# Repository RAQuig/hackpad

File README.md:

# hackpad
This respository was created by RAQuig for the project "Hackpad" by the charity Hack Club.
It is designed with three keyboard switches and USB input.
The repository currently includes:
    --> KiCAD files (.pcb, .prl, .pro, .sch, .sch-bak)
    --> 3D Print Files (.glb, .stl)
    --> QMK Configuration Files for firmware (potentially unstable release)
    --> The Bill of Materials (BOMCSV.csv)

README:
Description: This project is a very small homemade version of a Stream Deck. It has three keys that can be programmed and a small OLED display (0.91").
Why: I have always wanted to create my own technology and this project is my way in to the rest of it. I hope this project helps me learn a lot about how technology works.
How to use: Connect the USB cable to a laptop, PC, or (hopefully) console to get three keybinds to be used how I used and a OLED screen for some stats (controller battery level, FPS, Stream stats, etc.)

PCB: 
Schematic:

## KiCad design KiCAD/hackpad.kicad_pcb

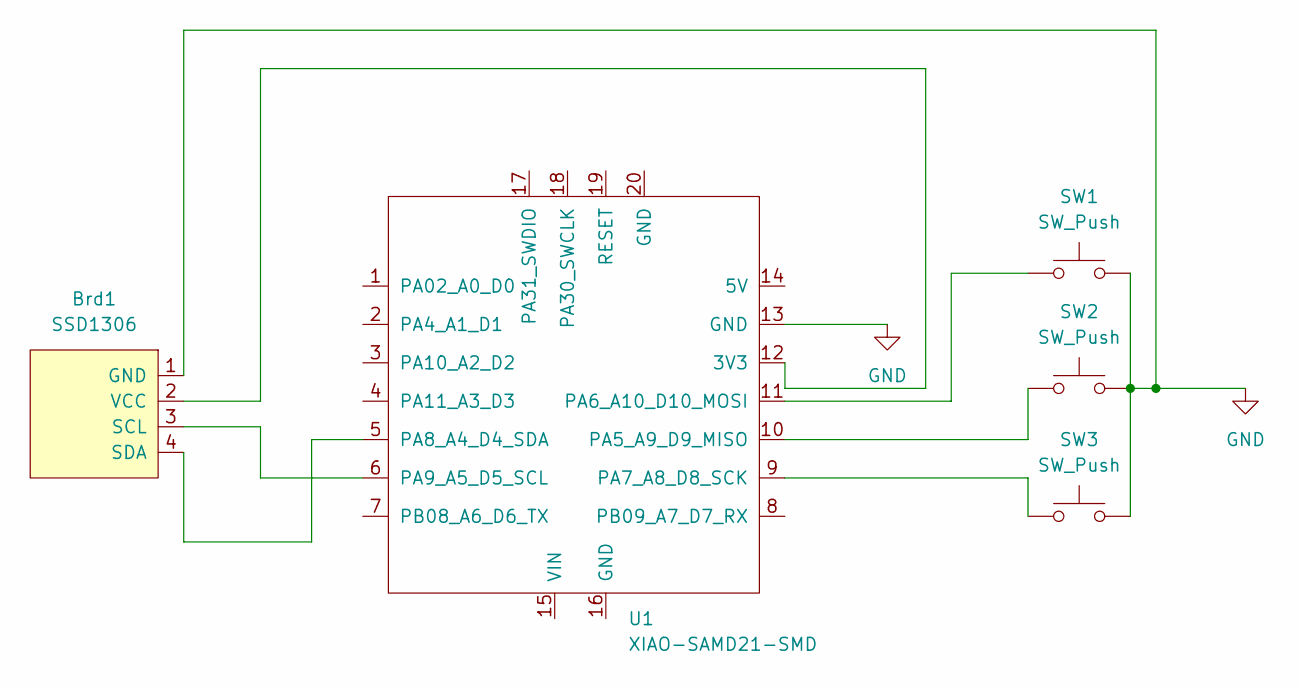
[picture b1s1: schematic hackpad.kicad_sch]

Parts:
Brd1: SSD1306; 128x64OLED
SW1, SW2, SW3: SW_Push; SW_Cherry_MX_1.00u_PCB
U1: XIAO-SAMD21-SMD; XIAO-Generic-Hybrid-14P-2.54-21X17.8MM

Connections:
GND: Brd1.1 (GND), SW1.2, SW2.2, SW3.2, U1.13 (GND)
unnamed: Brd1.3 (SCL), U1.6 (PA9_A5_D5_SCL)
unnamed: Brd1.4 (SDA), U1.5 (PA8_A4_D4_SDA)
unnamed: Brd1.2 (VCC), U1.12 (3V3)
unnamed: SW2.1, U1.10 (PA5_A9_D9_MISO)
unnamed: SW1.1, U1.11 (PA6_A10_D10_MOSI)
unnamed: SW3.1, U1.9 (PA7_A8_D8_SCK)

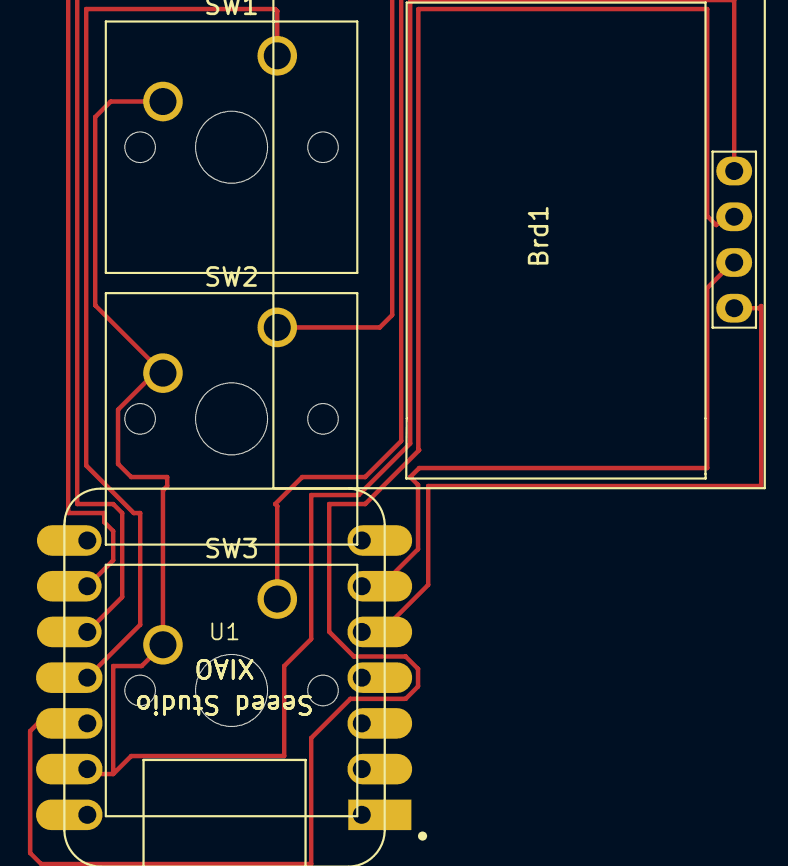
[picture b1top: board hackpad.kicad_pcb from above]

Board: 2 copper layers, 5 parts (0 on the bottom side), 7 nets.

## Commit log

2026-02-11 Added all files required
    Added 3D Design files (.stl, .glb) and all the KiCAD Project Files
2026-02-14 Created KiCAD folder
2026-02-14 Sorted all the files into folders
2026-02-14 Updated the README file
2026-02-15 Added files for Firmware flash
    Non-functional firmware files
2026-02-15 Moved non-fuctional firmware to /qmk/
2026-02-15 Deleted "/qmk/" due to linux breaking and files are no longer trusted and stable
2026-02-17 added (POTENTIALLY) Stable QMK firmware files
2026-02-17 QMK files added to /qmk/
2026-02-17 added QMK keymap
2026-02-17 Keymap moved to /qmk/keymaps/default/
2026-02-17 Update README to include QMK Configuration Files
    Added QMK Configuration Files section to README.
2026-02-17 Added BOM
2026-02-17 Add Bill of Materials to README
    Added Bill of Materials (BOMCSV.csv) to the list of included files.
2026-02-17 Enhanced README with project details and usage
2026-02-20 Deleted the old KiCad files to be replaced with the new KiCad files
2026-02-20 kiCAD file added
2026-02-20 Replaced and moved the KiCad files and removed the BOM to be replaced with a newer version
2026-02-20 Added Pictures to the REAME.md
2026-02-20 push message
2026-02-20 pushmessage
2026-02-20 Updated the README
2026-02-21 Updated the KiCad files to include the screen
